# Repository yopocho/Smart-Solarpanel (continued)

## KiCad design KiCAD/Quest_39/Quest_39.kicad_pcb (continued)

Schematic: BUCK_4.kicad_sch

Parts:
C59: 330uF; CP_Elec_8x6.9
C60, C61, C62: 22uF; C_0805_2012Metric
C63, C65, C66, C73: 100nF; C_0603_1608Metric
C64: 1uF; C_0603_1608Metric
C67: 10nF; C_0603_1608Metric
C68, C69, C70, C71: 100uF; C_1206_3216Metric
C72: 100pF; C_0603_1608Metric
JP4: SolderJumper_2_Bridged; SolderJumper-2_P1.3mm_Bridged_RoundedPad1.0x1.5mm
R38: 0R0025; R_1206_3216Metric
R39, R40: 10R; R_0805_2012Metric
R41: 9k; R_0805_2012Metric
R42: 1k; R_0805_2012Metric
R43: 10k; R_0805_2012Metric
R44: 20K; R_0805_2012Metric
TP27, TP28, TP29, TP30, TP31, TP32, TP33: TestPoint; TestPoint_Pad_D2.0mm
U16: AD626ANZ; DIP-8_W7.62mm_Socket_LongPads
U17: INA226; VSSOP-10_3x3mm_P0.5mm
U18: LTM4611EV-PBF; Linear_LGA-133_15.0x15.0mm_Layout12x12_P1.27mm
U19: MCP4151-502E/SN; MSOP-8_3x3mm_P0.65mm

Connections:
+5V: C63.1, C66.1, C73.1, U16.6 (+VS), U17.1 (A1), U17.6 (VS), U19.8 (VDD); also elsewhere on the board
/BUCK_4/+IN: R41.2, R42.1, U16.8 (+IN)
/BUCK_4/BUCK_VIN: C59.1, C60.1, C61.1, C62.1, R38.2, R40.1, R43.1, U18.A1 (VIN), U18.A2 (VIN), U18.A3 (VIN), U18.A4 (VIN), U18.A5 (VIN), U18.A6 (VIN), U18.B1 (VIN), U18.B2 (VIN), U18.B3 (VIN), U18.B4 (VIN), U18.B5 (VIN), U18.B6 (VIN), U18.C1 (VIN), U18.C2 (VIN), U18.C3 (VIN), U18.C4 (VIN), U18.C5 (VIN), U18.C6 (VIN)
/BUCK_4/P0A: R44.2, U19.5 (P0A)
/BUCK_4/RUN: R43.2, U18.A10 (RUN)
/BUCK_4/TRACK/SS: C67.2, U18.A9 (TRACK/SS)
/BUCK_4/Vfb: C72.2, R44.1, U18.F12 (VFB)
/BUCK_4/Vin+: C64.1, R39.2, U17.10 (Vin+)
/BUCK_4/Vin-: C64.2, R40.2, U17.9 (Vin-)
/CS4: U19.1 (*CS); also elsewhere on the board
/NEG_4: C59.2, C60.2, C61.2, C62.2, C67.1, C68.2, C69.2, C70.2, C71.2, R42.2, U16.1 (-IN), U18.A8 (MODE_PLLIN), U18.B7 (GND), U18.B9 (GND), U18.C7 (GND), U18.C9 (GND), U18.D1 (GND), U18.D2 (GND), U18.D3 (GND), U18.D4 (GND), U18.D5 (GND), U18.D6 (GND), U18.D8 (GND), U18.E1 (GND), U18.E2 (GND), U18.E3 (GND), U18.E4 (GND), U18.E5 (GND), U18.E6 (GND), U18.E7 (GND), U18.E9 (GND), U18.F1 (GND), U18.F2 (GND), U18.F3 (GND), U18.F4 (GND), U18.F5 (GND), U18.F6 (GND), U18.F7 (GND), U18.F8 (GND), U18.F9 (GND), U18.G1 (GND), U18.G2 (GND), U18.G3 (GND), U18.G4 (GND), U18.G5 (GND), U18.G6 (GND), U18.G7 (GND), U18.G8 (GND), U18.G9 (GND), U18.G11 (SGND), U18.H1 (GND), U18.H2 (GND), U18.H3 (GND), U18.H4 (GND), U18.H5 (GND), U18.H6 (GND), U18.H7 (GND), U18.H8 (GND), U18.H9 (GND), U18.H11 (SGND), U18.H12 (SGND), U18.M12 (VOSNS-), U19.6 (P0W); also elsewhere on the board
/NEG_5: C68.1, C69.1, C70.1, C71.1, C72.1, U18.J1 (VOUT), U18.J2 (VOUT), U18.J3 (VOUT), U18.J4 (VOUT), U18.J5 (VOUT), U18.J6 (VOUT), U18.J7 (VOUT), U18.J8 (VOUT), U18.J9 (VOUT), U18.J10 (VOUT), U18.J12 (VOSNS+), U18.K1 (VOUT), U18.K2 (VOUT), U18.K3 (VOUT), U18.K4 (VOUT), U18.K5 (VOUT), U18.K6 (VOUT), U18.K7 (VOUT), U18.K8 (VOUT), U18.K9 (VOUT), U18.K10 (VOUT), U18.K11 (VOUT), U18.L1 (VOUT), U18.L2 (VOUT), U18.L3 (VOUT), U18.L4 (VOUT), U18.L5 (VOUT), U18.L6 (VOUT), U18.L7 (VOUT), U18.L8 (VOUT), U18.L9 (VOUT), U18.L10 (VOUT), U18.L11 (VOUT), U18.M1 (VOUT), U18.M2 (VOUT), U18.M3 (VOUT), U18.M4 (VOUT), U18.M5 (VOUT), U18.M6 (VOUT), U18.M7 (VOUT), U18.M8 (VOUT), U18.M9 (VOUT), U18.M10 (VOUT), U18.M11 (VOUT); also elsewhere on the board
/PV_POS_4: R38.1, R39.1, R41.1; also elsewhere on the board
/SCK: U19.2 (SCK); also elsewhere on the board
/SCL: U17.5 (SCL); also elsewhere on the board
/SDA: U17.4 (SDA); also elsewhere on the board
/SDIO: U19.3 (SDI/SDO); also elsewhere on the board
GND: C63.2, C65.2, C66.2, C73.2, U16.2 (AGND), U16.3 (-VS), U17.2 (A0), U17.7 (GND), U19.4 (VSS); also elsewhere on the board
unnamed: C65.1, U16.4 (FILTER)
unnamed: JP4.1 (A), TP33.1, U18.K12 (DIFFVOUT)
unnamed: JP4.2 (B), TP32.1, U18.L12 (VOUT_LCL)
unnamed: TP27.1, U18.A7 (INTVCC)
unnamed: TP28.1, U16.5 (OUT), U17.8 (Vbus)
unnamed: TP29.1, U18.F11 (PGOOD), U18.G12 (PGOOD)
unnamed: TP30.1, U18.B12 (PLLFLTR/FSET)
unnamed: TP31.1, U18.A11 (COMP)

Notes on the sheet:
Addr=0x44
10:1 divider
Power Measurement
Extra mounting
the measured voltage is divided and then amplified by 10 as to simulate a follower. This is done to make use of the AD626 (low price and availability).
Adjustable Rfb
G=10
Output voltage is set by varying Rfb with a digipot. SPI = 00

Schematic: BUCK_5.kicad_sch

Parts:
C89: 330uF; CP_Elec_8x6.9
C90, C91, C92: 22uF; C_0805_2012Metric
C93, C95, C96, C103: 100nF; C_0603_1608Metric
C94: 1uF; C_0603_1608Metric
C97: 10nF; C_0603_1608Metric
C98, C99, C100, C101: 100uF; C_1206_3216Metric
C102: 100pF; C_0603_1608Metric
JP6: SolderJumper_2_Bridged; SolderJumper-2_P1.3mm_Bridged_RoundedPad1.0x1.5mm
R52: 0R0025; R_1206_3216Metric
R53, R54: 10R; R_0805_2012Metric
R55: 9k; R_0805_2012Metric
R56: 1k; R_0805_2012Metric
R57: 10k; R_0805_2012Metric
R58: 20K; R_0805_2012Metric
TP41, TP42, TP43, TP44, TP45, TP46, TP47: TestPoint; TestPoint_Pad_D2.0mm
U24: AD626ANZ; DIP-8_W7.62mm_Socket_LongPads
U25: INA226; VSSOP-10_3x3mm_P0.5mm
U26: LTM4611EV-PBF; Linear_LGA-133_15.0x15.0mm_Layout12x12_P1.27mm
U27: MCP4151-502E/SN; MSOP-8_3x3mm_P0.65mm

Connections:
+5V: C93.1, C96.1, C103.1, U24.6 (+VS), U25.1 (A1), U25.2 (A0), U25.6 (VS), U27.8 (VDD); also elsewhere on the board
/BUCK_5/+IN: R55.2, R56.1, U24.8 (+IN)
/BUCK_5/BUCK_VIN: C89.1, C90.1, C91.1, C92.1, R52.2, R54.1, R57.1, U26.A1 (VIN), U26.A2 (VIN), U26.A3 (VIN), U26.A4 (VIN), U26.A5 (VIN), U26.A6 (VIN), U26.B1 (VIN), U26.B2 (VIN), U26.B3 (VIN), U26.B4 (VIN), U26.B5 (VIN), U26.B6 (VIN), U26.C1 (VIN), U26.C2 (VIN), U26.C3 (VIN), U26.C4 (VIN), U26.C5 (VIN), U26.C6 (VIN)
/BUCK_5/P0A: R58.2, U27.5 (P0A)
/BUCK_5/RUN: R57.2, U26.A10 (RUN)
/BUCK_5/TRACK/SS: C97.2, U26.A9 (TRACK/SS)
/BUCK_5/Vfb: C102.2, R58.1, U26.F12 (VFB)
/BUCK_5/Vin+: C94.1, R53.2, U25.10 (Vin+)
/BUCK_5/Vin-: C94.2, R54.2, U25.9 (Vin-)
/CS5: U27.1 (*CS); also elsewhere on the board
/NEG_5: C89.2, C90.2, C91.2, C92.2, C97.1, C98.2, C99.2, C100.2, C101.2, R56.2, U24.1 (-IN), U26.A8 (MODE_PLLIN), U26.B7 (GND), U26.B9 (GND), U26.C7 (GND), U26.C9 (GND), U26.D1 (GND), U26.D2 (GND), U26.D3 (GND), U26.D4 (GND), U26.D5 (GND), U26.D6 (GND), U26.D8 (GND), U26.E1 (GND), U26.E2 (GND), U26.E3 (GND), U26.E4 (GND), U26.E5 (GND), U26.E6 (GND), U26.E7 (GND), U26.E9 (GND), U26.F1 (GND), U26.F2 (GND), U26.F3 (GND), U26.F4 (GND), U26.F5 (GND), U26.F6 (GND), U26.F7 (GND), U26.F8 (GND), U26.F9 (GND), U26.G1 (GND), U26.G2 (GND), U26.G3 (GND), U26.G4 (GND), U26.G5 (GND), U26.G6 (GND), U26.G7 (GND), U26.G8 (GND), U26.G9 (GND), U26.G11 (SGND), U26.H1 (GND), U26.H2 (GND), U26.H3 (GND), U26.H4 (GND), U26.H5 (GND), U26.H6 (GND), U26.H7 (GND), U26.H8 (GND), U26.H9 (GND), U26.H11 (SGND), U26.H12 (SGND), U26.M12 (VOSNS-), U27.6 (P0W); also elsewhere on the board
/NEG_6: C98.1, C99.1, C100.1, C101.1, C102.1, U26.J1 (VOUT), U26.J2 (VOUT), U26.J3 (VOUT), U26.J4 (VOUT), U26.J5 (VOUT), U26.J6 (VOUT), U26.J7 (VOUT), U26.J8 (VOUT), U26.J9 (VOUT), U26.J10 (VOUT), U26.J12 (VOSNS+), U26.K1 (VOUT), U26.K2 (VOUT), U26.K3 (VOUT), U26.K4 (VOUT), U26.K5 (VOUT), U26.K6 (VOUT), U26.K7 (VOUT), U26.K8 (VOUT), U26.K9 (VOUT), U26.K10 (VOUT), U26.K11 (VOUT), U26.L1 (VOUT), U26.L2 (VOUT), U26.L3 (VOUT), U26.L4 (VOUT), U26.L5 (VOUT), U26.L6 (VOUT), U26.L7 (VOUT), U26.L8 (VOUT), U26.L9 (VOUT), U26.L10 (VOUT), U26.L11 (VOUT), U26.M1 (VOUT), U26.M2 (VOUT), U26.M3 (VOUT), U26.M4 (VOUT), U26.M5 (VOUT), U26.M6 (VOUT), U26.M7 (VOUT), U26.M8 (VOUT), U26.M9 (VOUT), U26.M10 (VOUT), U26.M11 (VOUT); also elsewhere on the board
/PV_POS_5: R52.1, R53.1, R55.1; also elsewhere on the board
/SCK: U27.2 (SCK); also elsewhere on the board
/SCL: U25.5 (SCL); also elsewhere on the board
/SDA: U25.4 (SDA); also elsewhere on the board
/SDIO: U27.3 (SDI/SDO); also elsewhere on the board
GND: C93.2, C95.2, C96.2, C103.2, U24.2 (AGND), U24.3 (-VS), U25.7 (GND), U27.4 (VSS); also elsewhere on the board
unnamed: C95.1, U24.4 (FILTER)
unnamed: JP6.1 (A), TP47.1, U26.K12 (DIFFVOUT)
unnamed: JP6.2 (B), TP46.1, U26.L12 (VOUT_LCL)
unnamed: TP41.1, U26.A7 (INTVCC)
unnamed: TP42.1, U24.5 (OUT), U25.8 (Vbus)
unnamed: TP43.1, U26.F11 (PGOOD), U26.G12 (PGOOD)
unnamed: TP44.1, U26.B12 (PLLFLTR/FSET)
unnamed: TP45.1, U26.A11 (COMP)

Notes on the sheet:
Extra mounting
the measured voltage is divided and then amplified by 10 as to simulate a follower. This is done to make use of the AD626 (low price and availability).
10:1 divider
Output voltage is set by varying Rfb with a digipot. SPI = 00
Adjustable Rfb
Power Measurement
G=10
Addr=0x45

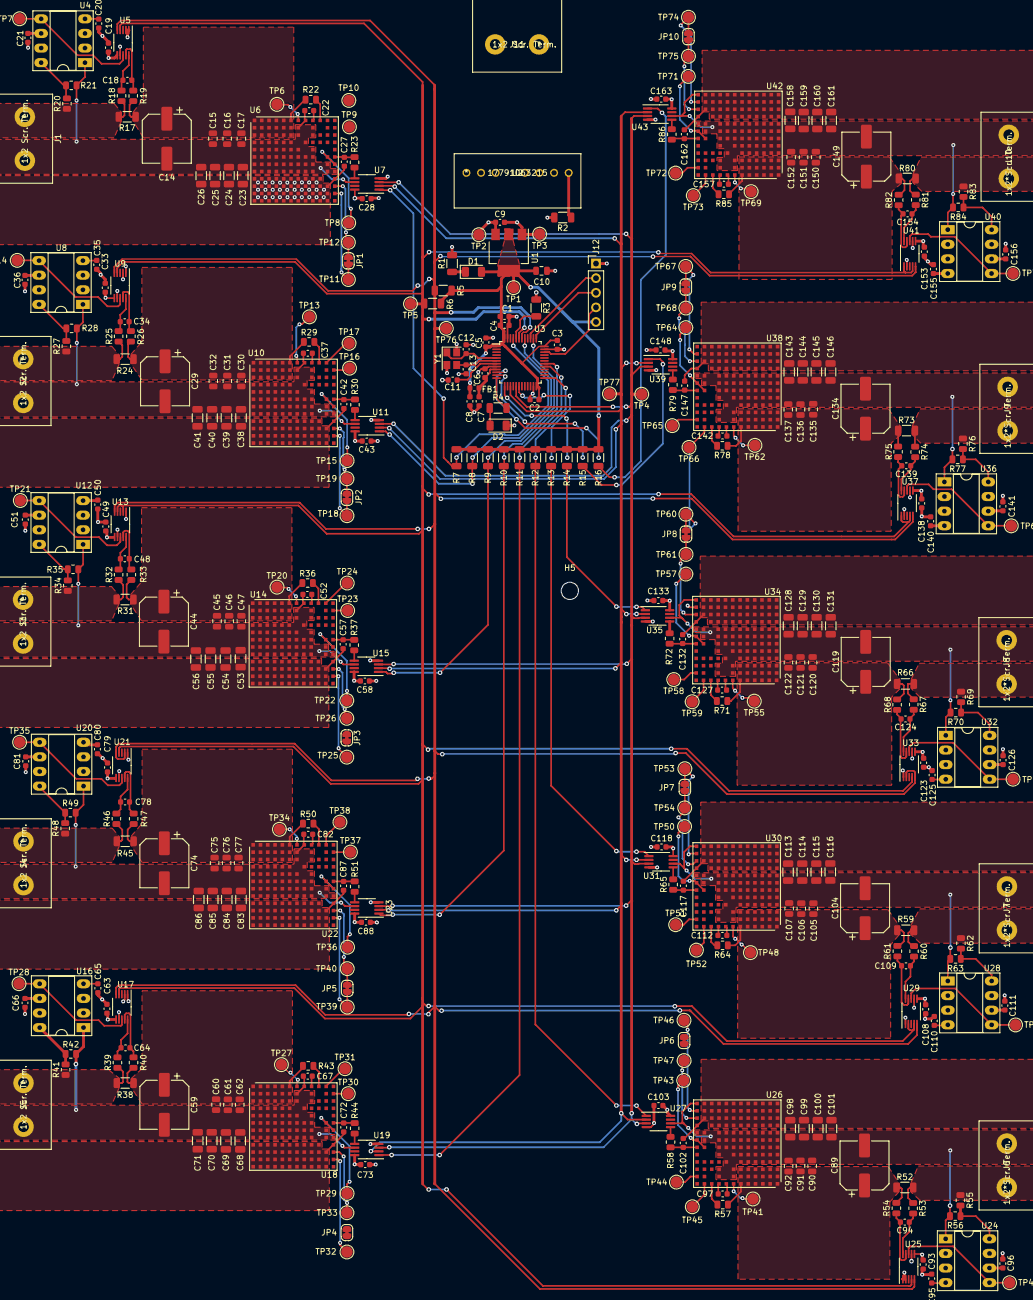
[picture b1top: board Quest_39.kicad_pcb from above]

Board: 4 copper layers, 400 parts (0 on the bottom side), 210 nets.

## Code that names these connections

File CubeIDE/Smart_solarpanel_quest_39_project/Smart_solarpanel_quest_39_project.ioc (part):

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Mcu.Name=STM32F103C(8-B)Tx
Mcu.Package=LQFP48
Mcu.UserName=STM32F103C8Tx
PA0-WKUP.GPIOParameters=GPIO_Label
PA0-WKUP.GPIO_Label=CS9
PA0-WKUP.Signal=GPIO_Output
PA1.GPIOParameters=GPIO_Label
PA1.GPIO_Label=CS8
PA1.Signal=GPIO_Output
PA13.Mode=Trace_Asynchronous_SW
PA13.Signal=SYS_JTMS-SWDIO
PA14.Mode=Trace_Asynchronous_SW
PA14.Signal=SYS_JTCK-SWCLK
PA15.GPIOParameters=GPIO_Label
PA15.GPIO_Label=CS2
PA15.Signal=GPIO_Output
PA3.GPIOParameters=GPIO_Label
PA3.GPIO_Label=CS7
PA3.Signal=GPIO_Output
PA5.Mode=Simplex_Bidirectional_Master
PA5.Signal=SPI1_SCK
PA7.Mode=Simplex_Bidirectional_Master
PA7.Signal=SPI1_MOSI
PA8.GPIOParameters=GPIO_Label
PA8.GPIO_Label=CS4
PA8.Signal=GPIO_Output
PA9.GPIOParameters=GPIO_Label
PA9.GPIO_Label=CS3
PA9.Signal=GPIO_Output
PB0.GPIOParameters=GPIO_Label
PB0.GPIO_Label=CS6
PB0.Signal=GPIO_Output
PB12.GPIOParameters=GPIO_Label
PB12.GPIO_Label=CS5
PB12.Signal=GPIO_Output
PB3.Mode=Trace_Asynchronous_SW
PB3.Signal=SYS_JTDO-TRACESWO
PB5.GPIOParameters=GPIO_Label
PB5.GPIO_Label=CS1
PB5.Signal=GPIO_Output
PB6.Mode=I2C
PB6.Signal=I2C1_SCL
PB7.Mode=I2C
PB7.Signal=I2C1_SDA
PB9.GPIOParameters=GPIO_Label
PB9.GPIO_Label=CS0
PB9.Signal=GPIO_Output
PD0-OSC_IN.Mode=HSE-External-Oscillator
PD0-OSC_IN.Signal=RCC_OSC_IN
PD1-OSC_OUT.Mode=HSE-External-Oscillator
PD1-OSC_OUT.Signal=RCC_OSC_OUT
RCC.SYSCLKFreq_VALUE=72000000
RCC.SYSCLKSource=RCC_SYSCLKSOURCE_PLLCLK
board=custom

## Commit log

2022-11-28 Add .gitattributes, .gitignore, and README.md.
2022-11-28 Add project files.
2022-11-28 Edited .gitignore
2022-11-28 Remove ignored files
2022-11-28 Added KiCAD to .gitignore and removed ignored files
2022-11-29 Updated .gitignore
2022-12-05 Edited schematic
2022-12-05 GND van INA226 verbonden, remote sense amplifier in gebruik genomen, labels aangepast en INTVCC not connected gemaakt.
2022-12-05 Ordered BUCK_x schematic pages
2022-12-06 Added screw terminals. Ordered nets and added seperation between systems.
2022-12-06 Changed root schematic to A3 size.
2022-12-08 Added libraries for special components
2022-12-12 Exchanged MCP601 for AD626
2022-12-12 Added library for 5V buck converter
2022-12-12 Added 3.3 and 5v power supplies
2022-12-12 Done TODO items
2022-12-12 Fixed most ERC errors
2022-12-12 Ordered and anotated components
2022-12-12 Small changes made during schematic review w/ Joost
2022-12-12 Added weak SPI CS pullups to prevent spurious behaviour
2022-12-13 Gave all INA226's unique addresses
2022-12-13 Removed all ERC errors
2022-12-13 Assigned all schem. symbols their footprints
2022-12-19 Initial work on layout
2022-12-19 Fixed INA226 schem. mistake and further layout work
2022-12-19 Completed first buck converter section PCB layout
2022-12-19 Partial wiring of first buck converter section PCB layout
2022-12-27 Added second buck converter section PCB layout
2023-01-09 Added 3rd buck converter section
2023-01-09 Placed 4th buck converter, started 5th.
2023-01-09 Finished placing 5th buck converter, started 6th
2023-01-10 Finished placing all LTM4611EV buck-converters
2023-01-10 Routed I2C SDA/SCL
2023-01-15 Switched to 4-layer stack-up w/ dedicated +5V and GND planes to improve EMI and make routing for PWR-traces easier
2023-01-16 Redid layout for the LTM4611EV Buck-converters (Issues with net-assignment to IC pads)
2023-01-16 Change routing of bypass caps, routed 3.3v to micro.
2023-01-17 Finished routing I2C, SPI and all 10 CS
2023-01-17 Top layer power planes added
2023-01-17 Executed DRC and fixed issues. Started work on bottom power planes
2023-01-17 Routed and stitched ~80% of the high current power planes
2023-01-17 Added quick to-do list on the layout page
2023-01-18 Finished ~90% of power planes. Added cosmetic silkscreen.
2023-01-18 Power planes 99% done. Improved and added more silkscreen.
2023-01-21 Added MOSFET bi-directional level-shifters to fix I2C between INA226's and STM32F103. Fixed mismatched via sizes.
2023-01-21 Fixed all DRC warnings. Improved some silkscreen.
2023-01-21 Miscellaneous silkscreen and improved component placement. Added PCB cutout to finalize dimensions.
2023-01-22 Added shielding vias to the I2C lines that run in-between the high-current power planes
2023-01-22 Added library to add silkscreen HU and UU logos
2023-01-22 Finally figured out where to place the middle mounting hole(s)
2023-01-22 Added image for README
2023-01-23 Added datasheet(s) to components for ease-of-use later
2023-01-31 Added all the SolidWorks files, edited README
